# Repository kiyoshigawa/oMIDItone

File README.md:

This is a project that takes an otamatone (https://otamatone.com/) and hijacks the control using digital potentiometers and a Teensy running USB MIDI libraries to turn it into a MIDI instrument.

The Controller PCB files currently use optoisolators. This design does not work correctly. I manually replaced the optoisolators with darlington NPN transistors, and that led to everything functioning as intended. I plan to revisit the PCB ocne I've tested the advanced features of the board (such as the servo control for opening the mouths, and the addressable LED lighting for the heads) to avoid needing more revisions.

The otamatone has had the touch-pot 'neck' removed and replaced with a connection to two MCP4151 digital potentiometers. I also had to connect two wires to the speaker outputs to get feedback on the frequency being played as the circuit is unstable over time and I could not map a resistance value to a given note accurately and reliably. I ended up removing the original PCBs from the heads and locating them centrally on my controller PCB to make wiring the heads and replacing damaged controllers easier. 

The current revision of the code is working with basic MIDI functionality, including note on, note off, and pitch bend. The pitch bending currently applies to every note currently being played. I intend to change it so that the pitch bend will apply to all the notes only on the MIDI channel it was sent on. This will allow multi-track MIDI files to send each track on a different channel so pitch bend will not effect all the tracks simultaneously. As far as I am aware, there is no way to differentiate tracks once the note messages are sent over MIDI if they are all sending to the same MIDI device, so per-track pitch bend is the best I can hope for given my single MIDI controller setup.

My goal is to finish the design and get all my planned features working with the current PCB, and then release a final version of the code and PCB for anyone who wants to follow in my crazy footsteps.

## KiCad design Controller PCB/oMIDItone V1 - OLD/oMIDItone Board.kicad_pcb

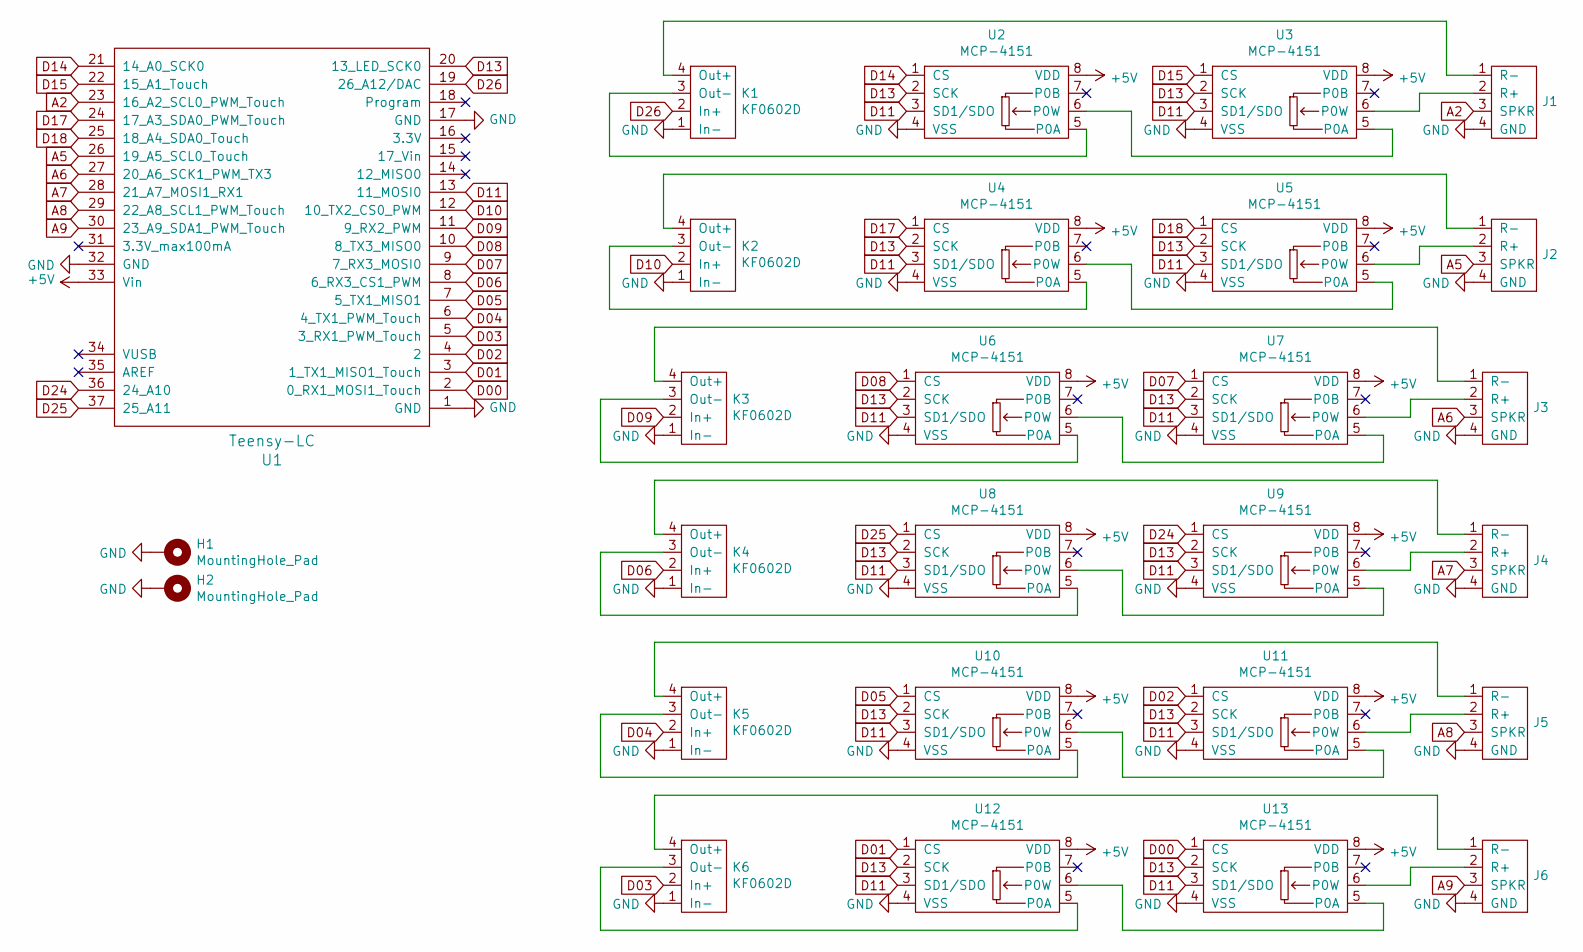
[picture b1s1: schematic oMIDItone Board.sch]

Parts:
H1, H2: MountingHole_Pad; MountingHole_3.2mm_M3_Pad_Via
J1, J2, J3, J4, J5, J6: oMIDItonePort; kioMIDItone COnnector
K1, K2, K3, K4, K5, K6: KF0602D
U1: Teensy-LC; Teensy_LC
U2, U3, U4, U5, U6, U7, U8, U9, U10, U11, U12, U13: MCP-4151; DIP-8_W7.62mm_LongPads

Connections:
+5V: U1.33 (Vin), U2.8 (VDD), U3.8 (VDD), U4.8 (VDD), U5.8 (VDD), U6.8 (VDD), U7.8 (VDD), U8.8 (VDD), U9.8 (VDD), U10.8 (VDD), U11.8 (VDD), U12.8 (VDD), U13.8 (VDD)
A2: J1.3 (SPKR), U1.23 (16_A2_SCL0_PWM_Touch)
A5: J2.3 (SPKR), U1.26 (19_A5_SCL0_Touch)
A6: J3.3 (SPKR), U1.27 (20_A6_SCK1_PWM_TX3)
A7: J4.3 (SPKR), U1.28 (21_A7_MOSI1_RX1)
A8: J5.3 (SPKR), U1.29 (22_A8_SCL1_PWM_Touch)
A9: J6.3 (SPKR), U1.30 (23_A9_SDA1_PWM_Touch)
D00: U1.2 (0_RX1_MOSI1_Touch), U13.1 (CS)
D01: U1.3 (1_TX1_MISO1_Touch), U12.1 (CS)
D02: U1.4 (2), U11.1 (CS)
D03: K6.2 (In+), U1.5 (3_RX1_PWM_Touch)
D04: K5.2 (In+), U1.6 (4_TX1_PWM_Touch)
D05: U1.7 (5_TX1_MISO1), U10.1 (CS)
D06: K4.2 (In+), U1.8 (6_RX3_CS1_PWM)
D07: U1.9 (7_RX3_MOSI0), U7.1 (CS)
D08: U1.10 (8_TX3_MISO0), U6.1 (CS)
D09: K3.2 (In+), U1.11 (9_RX2_PWM)
D10: K2.2 (In+), U1.12 (10_TX2_CS0_PWM)
D11: U1.13 (11_MOSI0), U2.3 (SD1/SDO), U3.3 (SD1/SDO), U4.3 (SD1/SDO), U5.3 (SD1/SDO), U6.3 (SD1/SDO), U7.3 (SD1/SDO), U8.3 (SD1/SDO), U9.3 (SD1/SDO), U10.3 (SD1/SDO), U11.3 (SD1/SDO), U12.3 (SD1/SDO), U13.3 (SD1/SDO)
D13: U1.20 (13_LED_SCK0), U2.2 (SCK), U3.2 (SCK), U4.2 (SCK), U5.2 (SCK), U6.2 (SCK), U7.2 (SCK), U8.2 (SCK), U9.2 (SCK), U10.2 (SCK), U11.2 (SCK), U12.2 (SCK), U13.2 (SCK)
D14: U1.21 (14_A0_SCK0), U2.1 (CS)
D15: U1.22 (15_A1_Touch), U3.1 (CS)
D17: U1.24 (17_A3_SDA0_PWM_Touch), U4.1 (CS)
D18: U1.25 (18_A4_SDA0_Touch), U5.1 (CS)
D24: U1.36 (24_A10), U9.1 (CS)
D25: U1.37 (25_A11), U8.1 (CS)
D26: K1.2 (In+), U1.19 (26_A12/DAC)
GND: H1.1, H2.1, J1.4 (GND), J2.4 (GND), J3.4 (GND), J4.4 (GND), J5.4 (GND), J6.4 (GND), K1.1 (In-), K2.1 (In-), K3.1 (In-), K4.1 (In-), K5.1 (In-), K6.1 (In-), U1.1 (GND), U1.17 (GND), U1.32 (GND), U2.4 (VSS), U3.4 (VSS), U4.4 (VSS), U5.4 (VSS), U6.4 (VSS), U7.4 (VSS), U8.4 (VSS), U9.4 (VSS), U10.4 (VSS), U11.4 (VSS), U12.4 (VSS), U13.4 (VSS)
unnamed: J1.1 (R-), K1.4 (Out+)
unnamed: J1.2 (R+), U3.6 (P0W)
unnamed: J2.1 (R-), K2.4 (Out+)
unnamed: J2.2 (R+), U5.6 (P0W)
unnamed: J3.1 (R-), K3.4 (Out+)
unnamed: J3.2 (R+), U7.6 (P0W)
unnamed: J4.1 (R-), K4.4 (Out+)
unnamed: J4.2 (R+), U9.6 (P0W)
unnamed: J5.1 (R-), K5.4 (Out+)
unnamed: J5.2 (R+), U11.6 (P0W)
unnamed: J6.1 (R-), K6.4 (Out+)
unnamed: J6.2 (R+), U13.6 (P0W)
unnamed: K1.3 (Out-), U2.5 (P0A)
unnamed: K2.3 (Out-), U4.5 (P0A)
unnamed: K3.3 (Out-), U6.5 (P0A)
unnamed: K4.3 (Out-), U8.5 (P0A)
unnamed: K5.3 (Out-), U10.5 (P0A)
unnamed: K6.3 (Out-), U12.5 (P0A)
unnamed: U2.6 (P0W), U3.5 (P0A)
unnamed: U4.6 (P0W), U5.5 (P0A)
unnamed: U6.6 (P0W), U7.5 (P0A)
unnamed: U8.6 (P0W), U9.5 (P0A)
unnamed: U10.6 (P0W), U11.5 (P0A)
unnamed: U12.6 (P0W), U13.5 (P0A)

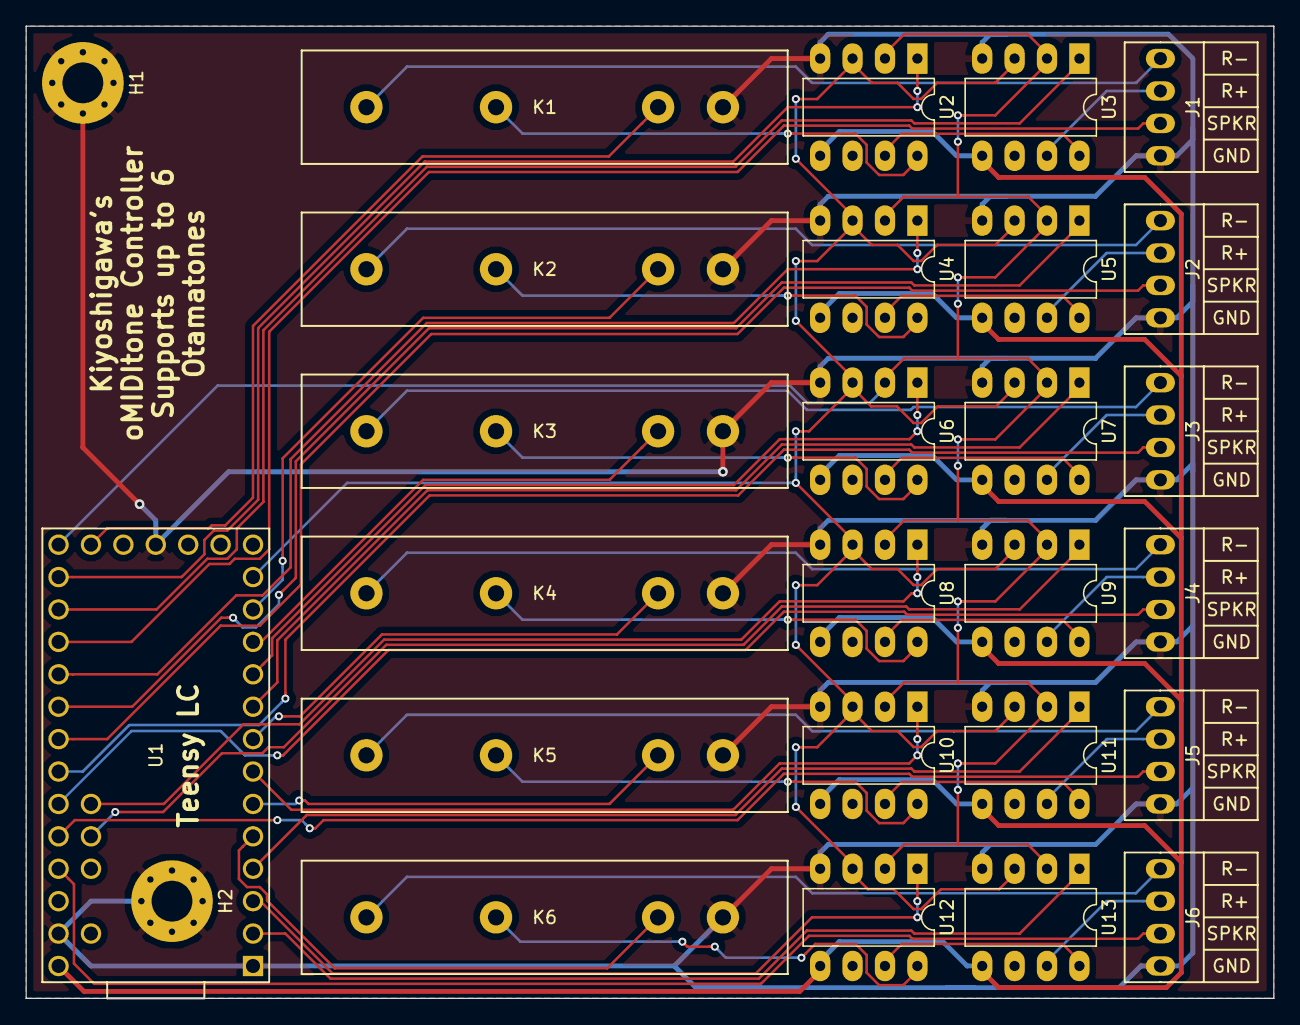
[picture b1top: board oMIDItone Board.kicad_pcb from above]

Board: 2 copper layers, 97.8 x 76.2 mm, 27 parts (0 on the bottom side), 52 nets.

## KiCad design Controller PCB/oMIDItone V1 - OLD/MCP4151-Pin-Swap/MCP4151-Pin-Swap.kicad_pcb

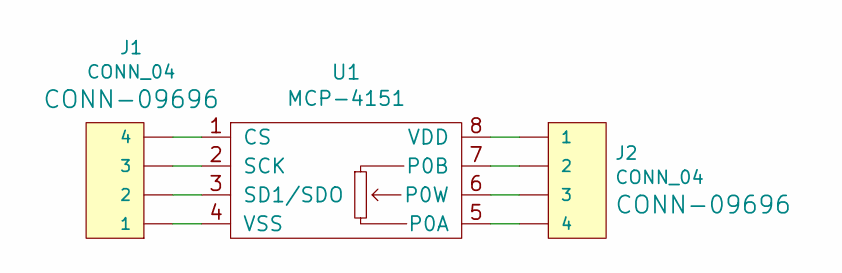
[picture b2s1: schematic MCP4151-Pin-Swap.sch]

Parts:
J1, J2: CONN_04; PinHeader_1x04_P2.54mm_Vertical
U1: MCP-4151; SOIC-8_3.9x4.9mm_P1.27mm

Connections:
unnamed: J1.1, U1.4 (VSS)
unnamed: J1.2, U1.3 (SD1/SDO)
unnamed: J1.3, U1.2 (SCK)
unnamed: J1.4, U1.1 (CS)
unnamed: J2.1, U1.8 (VDD)
unnamed: J2.2, U1.7 (P0B)
unnamed: J2.3, U1.6 (P0W)
unnamed: J2.4, U1.5 (P0A)

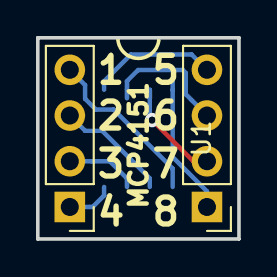
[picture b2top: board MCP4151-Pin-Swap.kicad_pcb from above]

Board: 2 copper layers, 11.2 x 11.2 mm, 3 parts (1 on the bottom side), 8 nets.

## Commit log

2019-03-26 Initial Class Commit - freq measure is broken
2019-03-27 Stabilization Working with fast ADC lib
2019-07-25 I don't know how to git.
2019-10-11 Several lighting modes, including VU_meter work
2019-11-06 Before I mess with frequency correction...
2019-11-10 Added MIDI CC Controls for Various Functions
2019-11-10 Fixed some bugs, left others...
2019-11-10 Offloaded all MIDI functions to MIDI_control.ino
2019-11-10 Got rid of the PROGMEM stuff - Wasn't used.
2019-11-10 Bug Fixes for FG and BG overriding themselves.
2019-11-17 Add Servo Position Control when Seros are Disabled
2019-11-17 Added Return to remove extra unassigned message
2019-11-18 Major measure_frequency() overhaul
2019-11-24 changed rainbow assignment to use a single array
2019-11-24 Changed head order to go from least recently used
2019-11-25 lighting all working, pitch bending still broken
2019-11-26 Pitch bending works, but is too slow.
2019-11-29 formatting cleanup, pitch still wonky
2019-12-02 About to mess everything up - pre change commit.
